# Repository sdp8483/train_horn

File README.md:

# Train Horn Synthesis with the MSP430FR2000
This readme is a short version of the blog post avalible on my personal website. Please read the blog post if you need more information: [link to blog]

## Introduction
The hardware and code presented is designed to simulate the sound of a train horn (or come as close as possible with the given hardware). Specifically is is designed to synthesize the sound of a [Leslie S-3L Locomotive Air Horn](http://www.dieselairhorns.com/sounds/LeslieS3L.mp3).

The final design is battery powered for portability. It uses a 18650 LiPo cell and features an onboard charger using a standard micro USB port and a low battery indicator LED.

The circuitry is able to drive a standard speaker load of 8-4Ω for mono sound. Four adjustable gain settings of 4, 8, 12, and 16 are available for setting the output volume of the audio amplifier with minimal modifications.

An onboard microcontroller generates the chord and enables the user control of the sound though a simple push button. The [MSP430FR2000](http://www.ti.com/product/MSP430FR2000) was chosen due to its low cost in single quantities and availability at the time of designing this product. The MSP430 line was chosen specifically to develop a familiarity with using the product.

## A Brief Overview

A 4-8Ω speaker is connected to the speaker terminal. The device is powered from a 18650 LiPo cell which is charged using the micro USB port, a blue LED indicates that the battery is charging. The charging circuitry is capable of charging the battery at a maximum current of 500mA.  The low battery detection circuitry will illuminate a red LED indicator light when the battery voltage is low and requires charging. The audio amplifier gain (volume) is configured using jumpers JP3-JP8 and is set to 16 by default. Pressing and holding either the small SMD or the larger right angle play button generates sound. A green LED is illuminated while sound is playing. Releasing the button stops sound generation.

## Schematic

## Detailed Description
### Sound Generation
The Leslie S-3L Locomotive Air Horn generates its distinctive [sound](http://www.dieselairhorns.com/sounds/LeslieS3L.mp3) using a three tone chord of approximately C, D#, and A [http://atsf.railfan.net/airhorns/s3l.html](http://atsf.railfan.net/airhorns/s3l.html).

The onboard microcontroller generates the chord using three 50% duty cycle PWM signals. Since the MSP430FR2000 microcontroller has only one general purpose timer the method outlined in TI app note [SLAA513A](http://www.ti.com/lit/an/slaa513a/slaa513a.pdf) was implemented to generate multiple time bases on a single MSP430 timer module. This enables use of the lower cost MSP430FR2000 instead of having to move to a potentially higher cost MSP430 microcontroller with three separate timer modules.

Each PWM signal from the microcontroller is passed through a three stage RC low pass filter to produce a sine wave on the output.  The RC low pass filter was designed with the help of the following online RC low pass filter calculator: [http://sim.okawa-denshi.jp/en/CRtool.php](http://sim.okawa-denshi.jp/en/CRtool.php)

After each PWM signal is converted to a sine wave the signals are then mixed together before entering the audio amplifier. The audio amplifier is a [TPA6211A1](http://www.ti.com/lit/ds/symlink/tpa6211a1.pdf) mono audio power amplifier. The audio amplifier has 4 adjustable gain settings that can be changed by desoldering the smd jumpers (JP3 to JP6) as indicated by the table. For example to set a gain of eight JP4, JP5, JP6, and JP7 would be removed from the PCB. The amplifier can drive a 4-8Ω speaker.

### Battery Circuitry
The circuit is powered with a standard 18650 LiPo cell. Be sure to observe polarity of the battery holder. The positive end of the battery installs opposite of the speaker terminal. Installing the battery in reverse polarity will destroy the battery charger IC and will damage the remaining circuitry. Don't ask me how I know.

Charging is controlled by the [MCP73831](https://www.microchip.com/wwwproducts/en/en024903) charge management IC at a maximum charging current of 500mA using the micro USB port. This USB port if for charging only, the data lines are not connected to the MSP430FR2000 microcontroller. A blue LED indicator is turned on while the battery charges. The LED turns off to indicate that the battery is fully charged.

A red LED is used to indicate a low battery voltage. The [MIC7221](http://ww1.microchip.com/downloads/en/DeviceDoc/mic7211.pdf) comparator is used to illuminate the LED when the battery voltage drops below ~3.3V. The internal 1.2V reference from the microcontroller is used as the voltage reference for the comparator.

The onboard comparator of the MSP430FR2000 was not used due to issues with getting it to function correctly, most likely error on my part. To save time and frustration an external comparator was used instead.

The MSP430FR2000 microcontroller has a maximum voltage supply rating of 3.6V requiring a 3.3V low dropout regulator to prevent a fully charged LiPo cell voltage of 4.2V damaging the microcontroller. SMD JP1 can be desoldered from the circuit to put the LDO in shutdown mode, turning off the microcontroller.

### Firmware
The microcontroller spends much of its time in a low power sleep mode, the full circuit draws about 0.3mA of quiescent current. A 1600mAh LiPo cell will have a standby life of over [3700 hours](https://www.digikey.com/en/resources/conversion-calculators/conversion-calculator-battery-life) or 154 days!

Sound is generated when the user presses and holds down the play button. There are two play buttons on the PCB, a small SMD button and a friendlier medium sized right angle button. The PCB was originally designed to use only the SMD button but a last minute change added the right angle through hole button. Both are populated to allow multiple options of triggering sound generation. The green LED indicator is used to indicate when the sound is being generated.

Firmware is avalible here: [firmware/train_horn_hold/train_horn_hold.c](firmware/train_horn_hold/train_horn_hold.c)

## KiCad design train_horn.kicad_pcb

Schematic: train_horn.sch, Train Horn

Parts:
BT1: 18650; 18650_battery_holder_PCB_Pins; Mfg Part Number BH-18650-PC-ND
C1, C4: 4.7uF; C_0805; Mfg Part Number CL21A475KQFNNNG
C2, C6, C8, C9, C10, C11, C12, C13, C14, C15, C16: 100nF; C_0805; Mfg Part Number CL21B104KOANNNC
C3, C5, C7, C20: 1uF; C_0805; Mfg Part Number CL21B105KOFNNNG
C17, C18, C19: 0.22uF; C_0805; Mfg Part Number CL21B224KAFNNNG
D1: BLUE; LED_0805_LIGHTPIPE; Mfg Part Number 150080BS75000
D2: RED; LED_0805_LIGHTPIPE; Mfg Part Number 150080RS75000
D3: GREEN; LED_0805_LIGHTPIPE; Mfg Part Number 150080GS75000
J1: USB_OTG; USB_Micro-B_Amphenol_10118192-0001LF; Mfg Part Number 10118192-0001LF
J2: PROG; Pin_Header_Straight_1x04_Pitch2.54mm
JP1: LDO_EN; R_1206_HandSoldering; Mfg Part Number RC1206JR-070RL
JP2: PROG_PWR; Pin_Header_Straight_1x02_Pitch2.54mm
JP3, JP4, JP5, JP6, JP7, JP8: GADJ; R_1206_HandSoldering; Mfg Part Number RC1206JR-070RL
LS1: Speaker; TerminalBlock_02x5mm_Straight
Q1: 2N7002; SOT-23; Mfg Part Number 2N7002K-T1-E3
R1, R4: 100K; R_0805; Mfg Part Number RC0805FR-07100KL
R2: 56K; R_0805; Mfg Part Number MCR10ERTF5602
R3: 470; R_0805; Mfg Part Number RC0805FR-07470RL
R5, R14: 1K; R_0805; Mfg Part Number RC0805FR-071KL
R6: 2k; R_0805; Mfg Part Number RC0805FR-072KL
R7: 47k; R_0805; Mfg Part Number NONE
R8, R11, R15: 6.2k; R_0805; Mfg Part Number RC0805FR-076K2L
R9, R12, R16: 5.1k; R_0805; Mfg Part Number RC0805FR-075K1L
R10, R13, R17: 3.6k; R_0805; Mfg Part Number RC0805FR-073K6L
R18, R19, R20, R21, R22, R23, R24, R25: 10k; R_0805; Mfg Part Number RC0805FR-0710KL
SW1: PLAY; SWITCH_Panasonic_SMDRight_EVQP7C; Mfg Part Number EVQ-P7C01P
TP1: P1.1; Test_Point_Pad_d1.5mm
TP2: P1.4; Test_Point_Pad_d1.5mm
TP3: P1.6; Test_Point_Pad_d1.5mm
TP4: P2.6; Test_Point_Pad_d1.5mm
TP5: P2.7; Test_Point_Pad_d1.5mm
U1: MIC7221; SOT-23-5; Mfg Part Number MIC7221YM5-TR
U2: MCP73831; SOT-23-5; Mfg Part Number MCP73831T-2ACI/OT
U3: TPS78233DDCR; TSOT-23-5; Mfg Part Number TPS78233DDCR
U4: MSP430FR2000_TSSOP; TSSOP-16_4.4x5mm_Pitch0.65mm; Mfg Part Number MSP430FR2000IPW16
U5: TPA6211A1; TPA6211A1_MSOP; Mfg Part Number TPA6211A1DGNR

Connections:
+3V3: C5.1, C6.1, C7.1, JP2.1, R7.1, U3.5 (OUT), U4.5 (DVCC)
A4: R10.2, U4.9 (P2.1)
B3: R8.2, U4.13 (P1.5)
D#4: R9.2, U4.10 (P2.0)
EN: JP1.1, U3.3 (EN)
GND: BT1.2 (-), C1.2, C2.2, C3.2, C4.2, C5.2, C6.2, C7.2, C8.2, C9.2, C10.2, C11.2, C12.2, C13.2, C14.2, C15.2, C16.2, C18.2, C19.2, C20.2, D3.1 (K), J1.5 (GND), J2.4, Q1.2, R2.2, R6.2, SW1.2, U1.5, U2.2 (Vss), U3.2 (GND), U3.4 (GND), U4.6 (DVSS), U5.7 (GND)
unnamed: C1.1, D1.2 (A), J1.1 (VBUS), U2.4 (Vdd)
unnamed: C8.1, R8.1, R11.2
unnamed: C9.1, R9.1, R12.2
unnamed: C10.1, R10.1, R13.2
unnamed: C11.1, R11.1, R15.2
unnamed: C12.1, R12.1, R16.2
unnamed: C13.1, R13.1, R17.2
unnamed: C14.1, C15.1, C16.1, C17.1, R15.1, R16.1, R17.1
unnamed: C17.2, JP3.2, R21.2
unnamed: C18.1, JP8.1, R22.2
unnamed: C19.1, U5.2 (BYPASS)
unnamed: D1.1 (K), R3.1
unnamed: D2.1 (K), Q1.3
unnamed: D2.2 (A), R5.2
unnamed: D3.2 (A), R14.1
unnamed: J2.1, JP2.2
unnamed: JP3.1, JP4.2, R20.2
unnamed: JP4.1, JP5.2, R19.2
unnamed: JP5.1, R18.2
unnamed: JP6.1, JP7.2, R24.2
unnamed: JP6.2, R25.2
unnamed: JP7.1, JP8.2, R23.2
unnamed: LS1.1, U5.8 (VO-)
unnamed: LS1.2, U5.5 (VO+)
unnamed: Q1.1, R4.2, U1.1
unnamed: R1.2, R2.1, U1.4
unnamed: R3.2, U2.1 (STAT)
unnamed: R6.1, U2.5 (PROG)
unnamed: R18.1, R19.1, R20.1, R21.1, U5.4 (IN-)
unnamed: R22.1, R23.1, R24.1, R25.1, U5.3 (IN+)
unnamed: TP1.1, U4.1 (P1.1)
unnamed: TP2.1, U4.14 (P1.4)
unnamed: TP3.1, U4.12 (P1.6)
unnamed: TP4.1, U4.8 (P2.6)
unnamed: TP5.1, U4.7 (P2.7)
PLAY: SW1.1, U4.15 (P1.3)
PLAY_LED: R14.2, U4.2 (P1.0)
SBWTCK: J2.3, U4.3 (TEST/SBWTCK)
SBWTDIO: J2.2, R7.2, U4.4 (~RST~/SBWTDIO)
VCC: BT1.1 (+), C2.1, C3.1, C4.1, C20.1, JP1.2, R1.1, R4.1, R5.1, U1.2, U2.3 (Vbat), U3.1 (IN), U5.6 (VDD)
VREF+: U1.3, U4.11 (P1.7)
~SHDWN: U4.16 (P1.2), U5.1 (~SHUTDOWN)

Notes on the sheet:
LiPo BATTERY AND CHARGING CIRCUIT
3V3 LDO FOR MSP430
EXT PROGRAMMING HEADER
Internal pullup is enabled in software, install pullup if internal is not enabled.
FREQUENCY FILTERING AND AMPLIFICATION
USER IO
1.2V±3.5%
BATTERY VOLTAGE INDICATOR
See Spreadsheet for Low Battery Range
MSP430FR MICROCONTROLLER
Gain
JP3
JP5
JP6
JP7
JP8
JP4
GAIN ADJUSTMENT

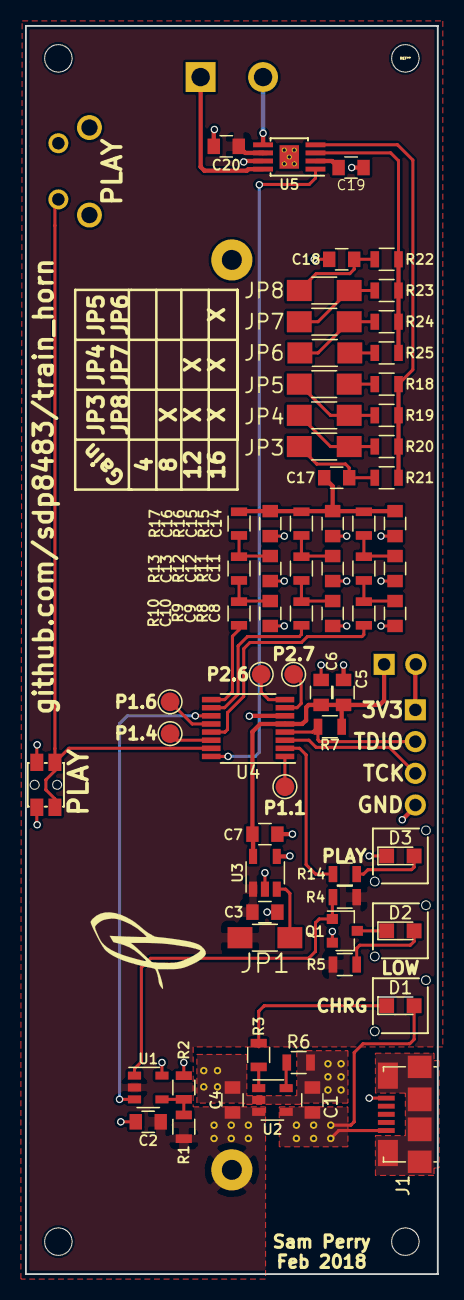
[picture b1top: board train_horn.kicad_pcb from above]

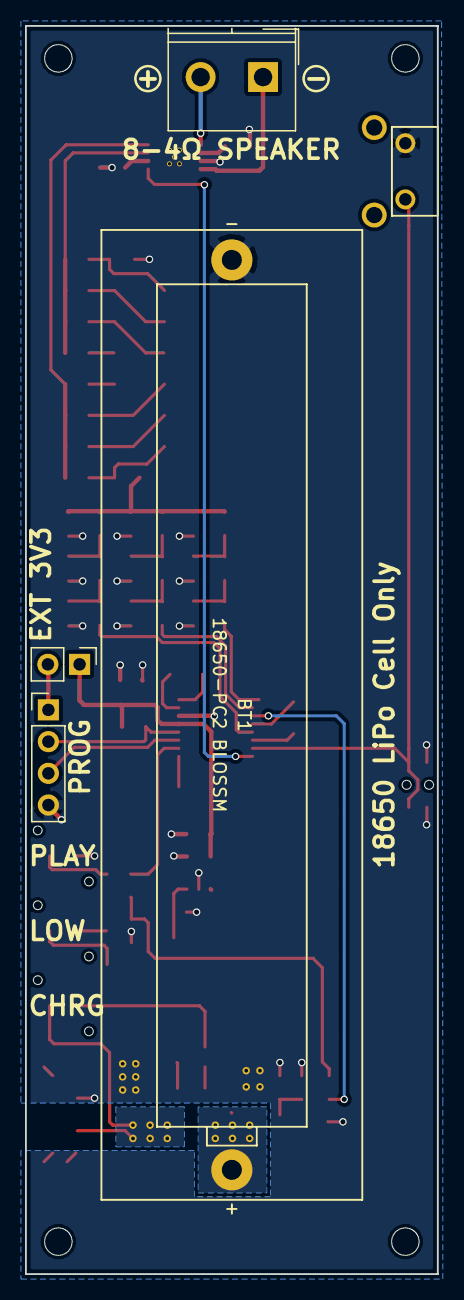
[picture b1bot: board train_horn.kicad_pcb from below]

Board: 2 copper layers, 33.0 x 100.0 mm, 72 parts (4 on the bottom side), 48 nets.

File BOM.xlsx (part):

Reference | Value | Footprint | Datasheet | Manufacture | Mfg Part Number | Package | Description
BT1 | 18650 | lib_fp:18650_battery_holder_PCB_Pins | http://www.memoryprotectiondevices.com/datasheets/BH-18650-P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 | MPD | BH-18650-PC-ND | PC PIN | HOLDER BATT 18650 1CELL PC PIN
C1 | 4.7uF | Capacitors_SMD:C_0805 | https://media.digikey.com/pdf/Data%20Sheets/Samsung%20PDFs/C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 | Samsung Electro-Mechanics | CL21A475KQFNNNG | 805 | CAP CER 4.7UF 6.3V X5R 0805
C10 | 100nF | Capacitors_SMD:C_0805 | https://media.digikey.com/pdf/Data%20Sheets/Samsung%20PDFs/C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 | Samsung Electro-Mechanics | CL21B104KOANNNC | 805 | CAP CER 0.1UF 16V X7R 0805
C11 | 100nF | Capacitors_SMD:C_0805 | https://media.digikey.com/pdf/Data%20Sheets/Samsung%20PDFs/C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 | Samsung Electro-Mechanics | CL21B104KOANNNC | 805 | CAP CER 0.1UF 16V X7R 0805
C12 | 100nF | Capacitors_SMD:C_0805 | https://media.digikey.com/pdf/Data%20Sheets/Samsung%20PDFs/C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 | Samsung Electro-Mechanics | CL21B104KOANNNC | 805 | CAP CER 0.1UF 16V X7R 0805
C13 | 100nF | Capacitors_SMD:C_0805 | https://media.digikey.com/pdf/Data%20Sheets/Samsung%20PDFs/C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 | Samsung Electro-Mechanics | CL21B104KOANNNC | 805 | CAP CER 0.1UF 16V X7R 0805
C14 | 100nF | Capacitors_SMD:C_0805 | https://media.digikey.com/pdf/Data%20Sheets/Samsung%20PDFs/C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 | Samsung Electro-Mechanics | CL21B104KOANNNC | 805 | CAP CER 0.1UF 16V X7R 0805
C15 | 100nF | Capacitors_SMD:C_0805 | https://media.digikey.com/pdf/Data%20Sheets/Samsung%20PDFs/C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 | Samsung Electro-Mechanics | CL21B104KOANNNC | 805 | CAP CER 0.1UF 16V X7R 0805
C16 | 100nF | Capacitors_SMD:C_0805 | https://media.digikey.com/pdf/Data%20Sheets/Samsung%20PDFs/C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 | Samsung Electro-Mechanics | CL21B104KOANNNC | 805 | CAP CER 0.1UF 16V X7R 0805
C17 | 0.22uF | Capacitors_SMD:C_0805 | https://media.digikey.com/pdf/Data%20Sheets/Samsung%20PDFs/C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 | Samsung Electro-Mechanics | CL21B224KAFNNNG | 805 | CAP CER 0.22UF 25V X7R 0805
C18 | 0.22uF | Capacitors_SMD:C_0805 | https://media.digikey.com/pdf/Data%20Sheets/Samsung%20PDFs/C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 | Samsung Electro-Mechanics | CL21B224KAFNNNG | 805 | CAP CER 0.22UF 25V X7R 0805
C19 | 0.22uF | Capacitors_SMD:C_0805 | https://media.digikey.com/pdf/Data%20Sheets/Samsung%20PDFs/C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 | Samsung Electro-Mechanics | CL21B224KAFNNNG | 805 | CAP CER 0.22UF 25V X7R 0805
C2 | 100nF | Capacitors_SMD:C_0805 | https://media.digikey.com/pdf/Data%20Sheets/Samsung%20PDFs/C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 | Samsung Electro-Mechanics | CL21B104KOANNNC | 805 | CAP CER 0.1UF 16V X7R 0805
C20 | 1uF | Capacitors_SMD:C_0805 | https://media.digikey.com/pdf/Data%20Sheets/Samsung%20PDFs/C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 | Samsung Electro-Mechanics | CL21B105KOFNNNG | 805 | CAP CER 1UF 16V X7R 0805
C3 | 1uF | Capacitors_SMD:C_0805 | https://media.digikey.com/pdf/Data%20Sheets/Samsung%20PDFs/C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 | Samsung Electro-Mechanics | CL21B105KOFNNNG | 805 | CAP CER 1UF 16V X7R 0805
C4 | 4.7uF | Capacitors_SMD:C_0805 | https://media.digikey.com/pdf/Data%20Sheets/Samsung%20PDFs/C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 | Samsung Electro-Mechanics | CL21A475KQFNNNG | 805 | CAP CER 4.7UF 6.3V X5R 0805
C5 | 1uF | Capacitors_SMD:C_0805 | https://media.digikey.com/pdf/Data%20Sheets/Samsung%20PDFs/C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 | Samsung Electro-Mechanics | CL21B105KOFNNNG | 805 | CAP CER 1UF 16V X7R 0805
C6 | 100nF | Capacitors_SMD:C_0805 | https://media.digikey.com/pdf/Data%20Sheets/Samsung%20PDFs/C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 | Samsung Electro-Mechanics | CL21B104KOANNNC | 805 | CAP CER 0.1UF 16V X7R 0805
C7 | 1uF | Capacitors_SMD:C_0805 | https://media.digikey.com/pdf/Data%20Sheets/Samsung%20PDFs/C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 | Samsung Electro-Mechanics | CL21B105KOFNNNG | 805 | CAP CER 1UF 16V X7R 0805
C8 | 100nF | Capacitors_SMD:C_0805 | https://media.digikey.com/pdf/Data%20Sheets/Samsung%20PDFs/C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 | Samsung Electro-Mechanics | CL21B104KOANNNC | 805 | CAP CER 0.1UF 16V X7R 0805
C9 | 100nF | Capacitors_SMD:C_0805 | https://media.digikey.com/pdf/Data%20Sheets/Samsung%20PDFs/C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 | Samsung Electro-Mechanics | CL21B104KOANNNC | 805 | CAP CER 0.1UF 16V X7R 0805
D1 | BLUE | lib_fp:LED_0805_LIGHTPIPE | http://katalog.we-online.de/led/datasheet/150080BS75000.pdf | Wurth Electronics Inc. | 150080BS75000 | 805 | Blue 470nm LED Indication
D2 | RED | lib_fp:LED_0805_LIGHTPIPE | http://katalog.we-online.de/led/datasheet/150080RS75000.pdf | Wurth Electronics Inc. | 150080RS75000 | 805 | LED RED CLEAR 0805 SMD
D3 | GREEN | lib_fp:LED_0805_LIGHTPIPE | http://katalog.we-online.de/led/datasheet/150080GS75000.pdf | Wurth Electronics Inc. | 150080GS75000 | 805 | LED GREEN CLEAR 0805 SMD
J1 | USB_OTG | lib_fp:USB_Micro-B_Amphenol_10118192-0001LF | https://cdn.amphenol-icc.com/media/wysiwyg/files/drawing/101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 | Amphenol | 10118192-0001LF | USB MICRO B | CONN USB MICRO B RECPT SMT R/A
J2 | PROG | Pin_Headers:Pin_Header_Straight_1x04_Pitch2.54mm |  |  |  | PC PIN | CONN HEADER 4 POS 2.54
JP1 | LDO_EN | Resistors_SMD:R_1206_HandSoldering | http://www.yageo.com/documents/recent/PYu-RC_Group_51_RoHS_L_8.pdf | Yageo | RC1206JR-070RL | 1206 | RES SMD 0 OHM JUMPER 1/4W 1206
JP2 | PROG_PWR | Pin_Headers:Pin_Header_Straight_1x02_Pitch2.54mm |  |  |  | PC PIN | CONN HEADER 2 POS 2.54
JP3 | GADJ | Resistors_SMD:R_1206_HandSoldering | http://www.yageo.com/documents/recent/PYu-RC_Group_51_RoHS_L_8.pdf | Yageo | RC1206JR-070RL | 1206 | RES SMD 0 OHM JUMPER 1/4W 1206
JP4 | GADJ | Resistors_SMD:R_1206_HandSoldering | http://www.yageo.com/documents/recent/PYu-RC_Group_51_RoHS_L_8.pdf | Yageo | RC1206JR-070RL | 1206 | RES SMD 0 OHM JUMPER 1/4W 1206
JP5 | GADJ | Resistors_SMD:R_1206_HandSoldering | http://www.yageo.com/documents/recent/PYu-RC_Group_51_RoHS_L_8.pdf | Yageo | RC1206JR-070RL | 1206 | RES SMD 0 OHM JUMPER 1/4W 1206
JP6 | GADJ | Resistors_SMD:R_1206_HandSoldering | http://www.yageo.com/documents/recent/PYu-RC_Group_51_RoHS_L_8.pdf | Yageo | RC1206JR-070RL | 1206 | RES SMD 0 OHM JUMPER 1/4W 1206
JP7 | GADJ | Resistors_SMD:R_1206_HandSoldering | http://www.yageo.com/documents/recent/PYu-RC_Group_51_RoHS_L_8.pdf | Yageo | RC1206JR-070RL | 1206 | RES SMD 0 OHM JUMPER 1/4W 1206
JP8 | GADJ | Resistors_SMD:R_1206_HandSoldering | http://www.yageo.com/documents/recent/PYu-RC_Group_51_RoHS_L_8.pdf | Yageo | RC1206JR-070RL | 1206 | RES SMD 0 OHM JUMPER 1/4W 1206
LS1 | Speaker | lib_fp:TerminalBlock_02x5mm_Straight |  |  |  | PC PIN | 2POS 5MM SCREW TERMINAL BLOCK
Q1 | 2N7002 | TO_SOT_Packages_SMD:SOT-23 | http://www.vishay.com/docs/71333/2n7002k.pdf | Vishay Siliconix | 2N7002K-T1-E3 | SOT-23 | MOSFET N-CH 60V 300MA SOT-23
R1 | 100K | Resistors_SMD:R_0805 | http://www.yageo.com/documents/recent/PYu-RC_Group_51_RoHS_L_8.pdf | Yageo | RC0805FR-07100KL | 805 | RES SMD 100K OHM 1% 1/8W 0805
R10 | 3.6k | Resistors_SMD:R_0805 | http://www.yageo.com/documents/recent/PYu-RC_Group_51_RoHS_L_8.pdf | Yageo | RC0805FR-073K6L | 805 | RES SMD 3.6K OHM 1% 1/8W 0805
R11 | 6.2k | Resistors_SMD:R_0805 | http://www.yageo.com/documents/recent/PYu-RC_Group_51_RoHS_L_8.pdf | Yageo | RC0805FR-076K2L | 805 | RES SMD 6.2K OHM 1% 1/8W 0805
R12 | 5.1k | Resistors_SMD:R_0805 | http://www.yageo.com/documents/recent/PYu-RC_Group_51_RoHS_L_8.pdf | Yageo | RC0805FR-075K1L | 805 | RES SMD 5.1K OHM 1% 1/8W 0805
R13 | 3.6k | Resistors_SMD:R_0805 | http://www.yageo.com/documents/recent/PYu-RC_Group_51_RoHS_L_8.pdf | Yageo | RC0805FR-073K6L | 805 | RES SMD 3.6K OHM 1% 1/8W 0805
R14 | 1K | Resistors_SMD:R_0805 | http://www.yageo.com/documents/recent/PYu-RC_Group_51_RoHS_L_8.pdf | Yageo | RC0805FR-071KL | 805 | RES SMD 1K OHM 1% 1/8W 0805
R15 | 6.2k | Resistors_SMD:R_0805 | http://www.yageo.com/documents/recent/PYu-RC_Group_51_RoHS_L_8.pdf | Yageo | RC0805FR-076K2L | 805 | RES SMD 6.2K OHM 1% 1/8W 0805
R16 | 5.1k | Resistors_SMD:R_0805 | http://www.yageo.com/documents/recent/PYu-RC_Group_51_RoHS_L_8.pdf | Yageo | RC0805FR-075K1L | 805 | RES SMD 5.1K OHM 1% 1/8W 0805
R17 | 3.6k | Resistors_SMD:R_0805 | http://www.yageo.com/documents/recent/PYu-RC_Group_51_RoHS_L_8.pdf | Yageo | RC0805FR-073K6L | 805 | RES SMD 3.6K OHM 1% 1/8W 0805
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
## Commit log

2018-02-05 inital commit
2018-02-08 not using internal comparitor for now, must solve problem of comparitor and timer not working together
2018-02-08 create audio amplifier symbol
2018-02-08 add audio amplifier to circuit rearange page layout remove comparitor references
2018-02-09 comparator now works thanks to help from TI E2E
2018-02-10 comparator does not function correctly, using external circuitry
2018-02-11 initial final schematic
2018-02-11 pin swaps, audio amp shutdown
2018-02-11 ignore temp xlsx files
2018-02-11 initial calculations, ugly spreadsheet
2018-02-11 schematic annotation
2018-02-12 project specific footprints
2018-02-12 swap speaker pins 1 and 2 to aid pcb layout
2018-02-12 no clue what this does but here it is
2018-02-12 start pcb layout
2018-02-13 setting large componet location. Change PCB size
2018-02-15 moving things around
2018-02-18 add smd tact switch footprint
2018-02-18 add manufacture suggested footprint
2018-02-18 vias for stitching
2018-02-18 fancy up silskscreen, cortyard, fab outline
2018-02-18 fancy up footprint
2018-02-18 add silkscreen
2018-02-18 laying things out
2018-02-18 move play button to P1.3 for PCB layout reasons
2018-02-19 finising touches on silkscreen
2018-02-19 add 9mm x 6mm P logo
2018-02-19 moved silkscreen L in from front
2018-02-19 add 3d models to PCB
2018-02-20 update schematic component description fields
2018-02-20 generate BOM
2018-02-20 update LED ref to reflect ref on schematic
2018-02-20 not sure how these got here, dont need for kicad 3d viewer. Must have been from FreeCAD script.
2018-02-21 removed dimension callout to switch center
2018-02-21 plot gerber output for manufacture
2018-02-21 save after gerber output
2018-02-23 add alternative tact switch footprint and 3D model
2018-02-23 add TH tact switch in place of microSMD switch, retained SMD switch as option
2018-02-23 KiCAD StepUp FreeCAD PCB to step
2018-02-23 replot gerber and drill files
2018-02-25 initial commit, play while button is held
2018-02-25 update low note frequency to 256Hz change io to #defines and cleaned up comments
2018-02-25 on initial start there would be a pause between pushing the play button and sound generation setting an inital value for timer_b seems to fix this
2018-02-25 ignore complied code
2018-02-28 format data to table
2018-03-02 clean up component discriptions
2018-03-02 R7 add note in discription not to populate
2018-03-02 R10, R13, R17 update from super expensive 0.1% resistor to reasonable 1%
    For some reason I chose a super expensive 3.6K 0.1% resistor when all the others are 1%. No need for super presision.
2018-03-02 project save after changes
2018-03-02 update gain jumper fields
2018-03-02 update BOM with corrected fields
    Removed TP from bom list
2018-03-02 implement software loop to prevent lockup
    if button is double tapped microcontoller may lock up. Added software loop after button is relased to prevent button from being pressed so quickly.
2018-03-05 circuit annotations
2018-03-06 fix manufacture name in descriptions
    R5 and R14 had links instead of names in the manufacture description fields
2018-03-06 MCP7383 missing fields filled
    MCP7383 info fields were not filled out, corrected with porper info
2018-03-06 ignore temp fods files
2018-03-06 blue led description style same as all components
    style points +1
2018-03-06 add detailed BOM cost and pricing
2018-03-06 better BOM replaces this
2018-03-07 printing formating
2018-03-07 include alternative play switch
2018-03-11 plot schematic to pdf
2018-03-11 images for blog/ readme
2018-03-12 more photos for blog
2018-03-18 video thumbnail image
2018-03-18 Update Readme to be better
2018-03-18 spaces before images are cool
2018-03-18 more info elsewhere
2020-06-07 find missing libs / remap to new kicad version
2020-06-07 generate iBOM
